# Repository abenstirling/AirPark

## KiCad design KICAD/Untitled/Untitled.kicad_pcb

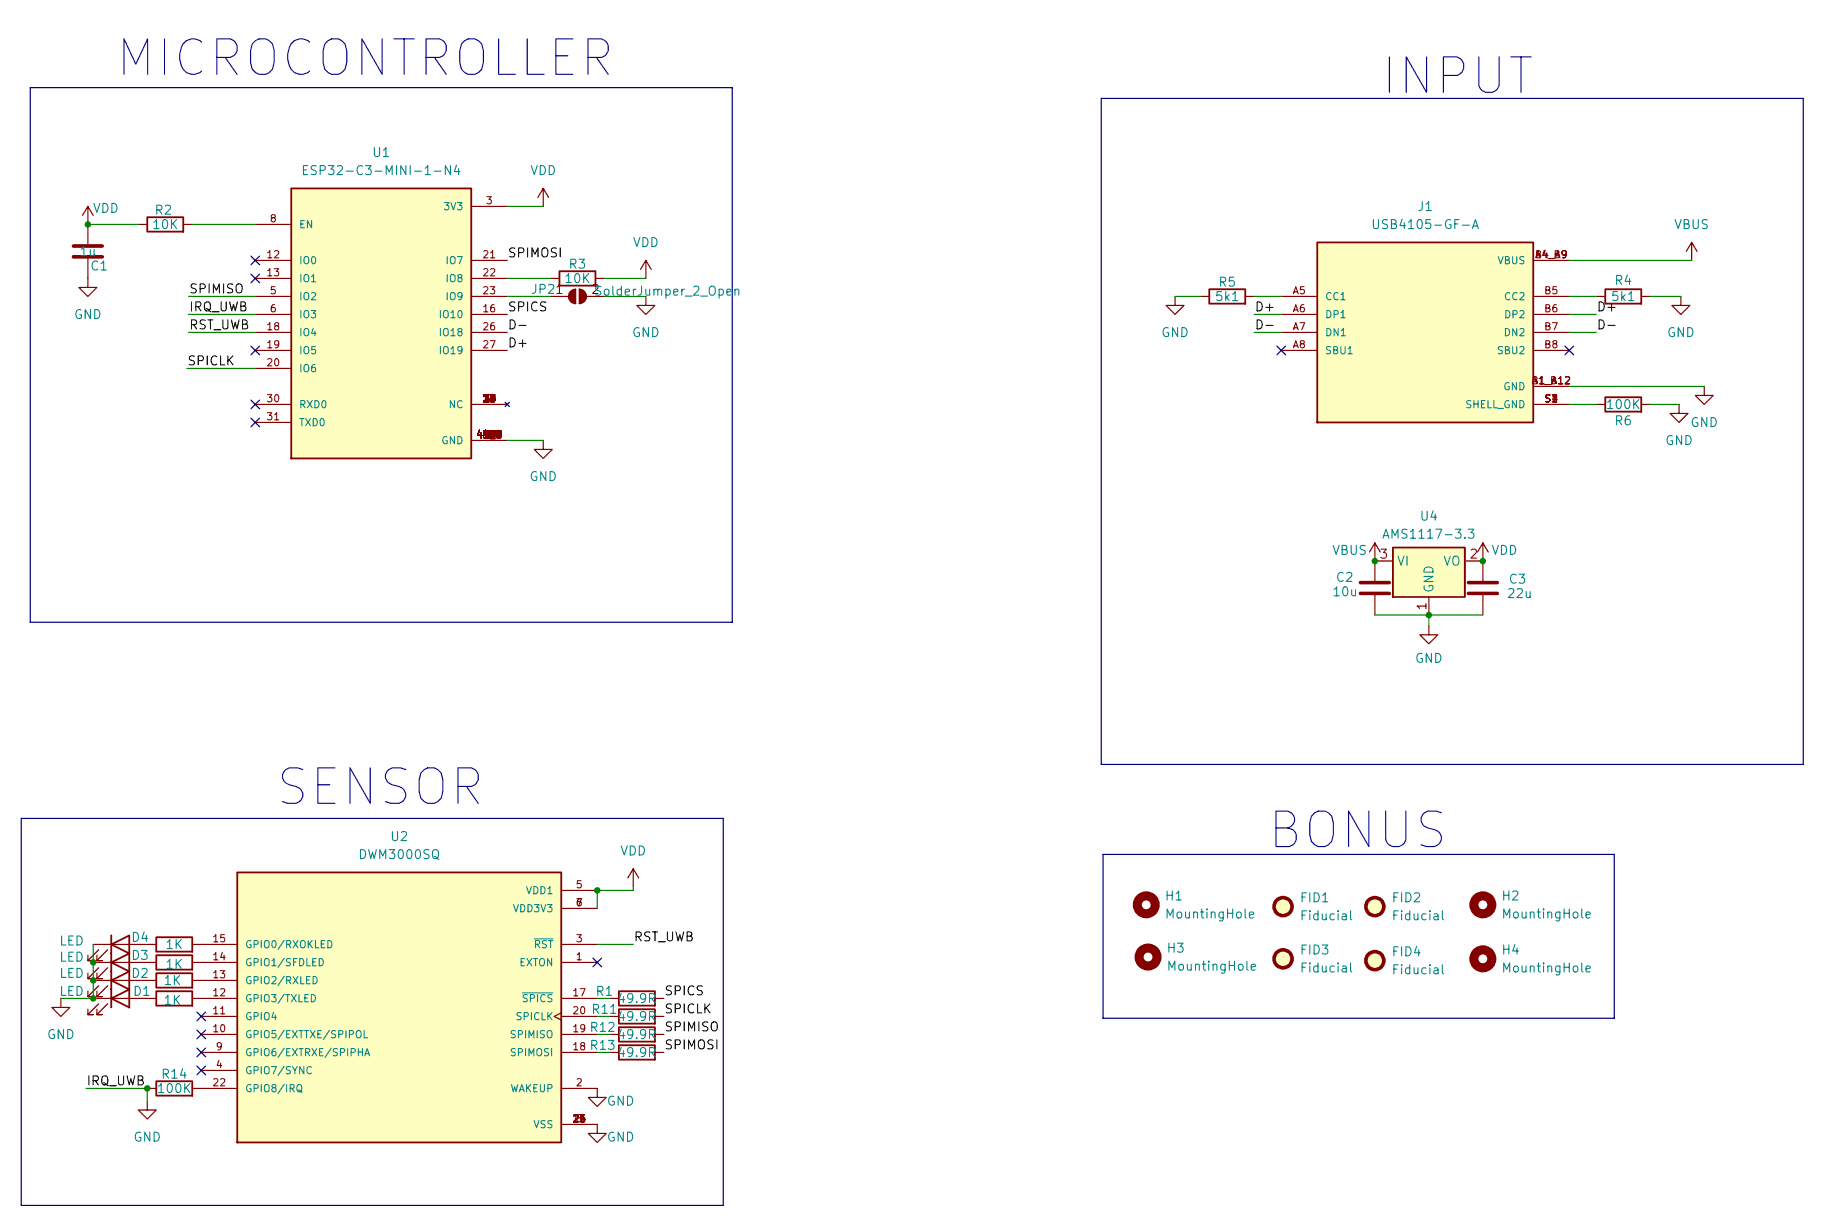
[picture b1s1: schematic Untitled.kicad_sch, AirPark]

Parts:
C1: 1u; C_0603_1608Metric
C2: 10u; C_0603_1608Metric
C3: 22u; C_0603_1608Metric
D1, D2, D3, D4: LED; LED_0603_1608Metric
FID1, FID2, FID3, FID4: Fiducial; Fiducial_1mm_Mask2mm
H1, H2, H3, H4: MountingHole; MountingHole_3.2mm_M3_DIN965_Pad
J1: USB4105-GF-A; GCT_USB4105-GF-A; PARTREV A3
JP2: SolderJumper_2_Open; SolderJumper-2_P1.3mm_Open_Pad1.0x1.5mm
R1, R11, R12, R13: 49.9R; R_0603_1608Metric
R2, R3: 10K; R_0603_1608Metric
R4, R5: 5k1; R_0603_1608Metric
R6, R14: 100K; R_0603_1608Metric
R7, R8, R9, R10: 1K; R_0603_1608Metric
U1: ESP32-C3-MINI-1-N4; XCVR_ESP32-C3-MINI-1-N4; PARTREV v1.0
U2: DWM3000SQ; XCVR_DWM3000SQ; PARTREV B
U4: AMS1117-3.3; SOT-223-3_TabPin2

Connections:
/D+: J1.A6 (DP1), J1.B6 (DP2), U1.27 (IO19)
/D-: J1.A7 (DN1), J1.B7 (DN2), U1.26 (IO18)
/RST_UWB: U1.18 (IO4), U2.3 (~RST)
/SPICLK: R11.2, U1.20 (IO6)
/SPICS: R1.2, U1.16 (IO10)
/SPIMISO: R12.2, U1.5 (IO2)
/SPIMOSI: R13.2, U1.21 (IO7)
GND: C1.2, C2.2, C3.2, D1.1 (K), D2.1 (K), D3.1 (K), D4.1 (K), J1.A1_B12 (GND), J1.B1_A12 (GND), JP2.2 (B), R4.2, R5.1, R6.2, R14.1, U1.1 (GND), U1.2 (GND), U1.6 (IO3), U1.11 (GND), U1.14 (GND), U1.36 (GND), U1.37 (GND), U1.38 (GND), U1.39 (GND), U1.40 (GND), U1.41 (GND), U1.42 (GND), U1.43 (GND), U1.44 (GND), U1.45 (GND), U1.46 (GND), U1.47 (GND), U1.48 (GND), U1.49_1 (GND), U1.49_2 (GND), U1.49_3 (GND), U1.49_4 (GND), U1.49_5 (GND), U1.49_6 (GND), U1.49_7 (GND), U1.49_8 (GND), U1.49_9 (GND), U1.50 (GND), U1.51 (GND), U1.52 (GND), U1.53 (GND), U2.2 (WAKEUP), U2.8 (VSS), U2.16 (VSS), U2.21 (VSS), U2.23 (VSS), U2.24 (VSS), U4.1 (GND)
unnamed: D1.2 (A), R10.1
unnamed: D2.2 (A), R7.1
unnamed: D3.2 (A), R8.1
unnamed: D4.2 (A), R9.1
unnamed: J1.A5 (CC1), R5.2
unnamed: J1.B5 (CC2), R4.1
unnamed: J1.S1 (SHELL_GND), J1.S2 (SHELL_GND), J1.S3 (SHELL_GND), J1.S4 (SHELL_GND), R6.1
unnamed: JP2.1 (A), U1.23 (IO9)
unnamed: R2.2, U1.8 (EN)
unnamed: R3.1, U1.22 (IO8)
unnamed: R9.2, U2.15 (GPIO0/RXOKLED)
unnamed: R8.2, U2.14 (GPIO1/SFDLED)
unnamed: R7.2, U2.13 (GPIO2/RXLED)
unnamed: R10.2, U2.12 (GPIO3/TXLED)
unnamed: R14.2, U2.22 (GPIO8/IRQ)
unnamed: R11.1, U2.20 (SPICLK)
unnamed: R12.1, U2.19 (SPIMISO)
unnamed: R13.1, U2.18 (SPIMOSI)
unnamed: R1.1, U2.17 (~SPICS)
VBUS: C2.1, J1.A4_B9 (VBUS), J1.B4_A9 (VBUS), U4.3 (VI)
VDD: C1.1, C3.1, R2.1, R3.2, U1.3 (3V3), U2.5 (VDD1), U2.6 (VDD3V3), U2.7 (VDD3V3), U4.2 (VO)

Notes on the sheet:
BONUS
MICROCONTROLLER
INPUT
SENSOR

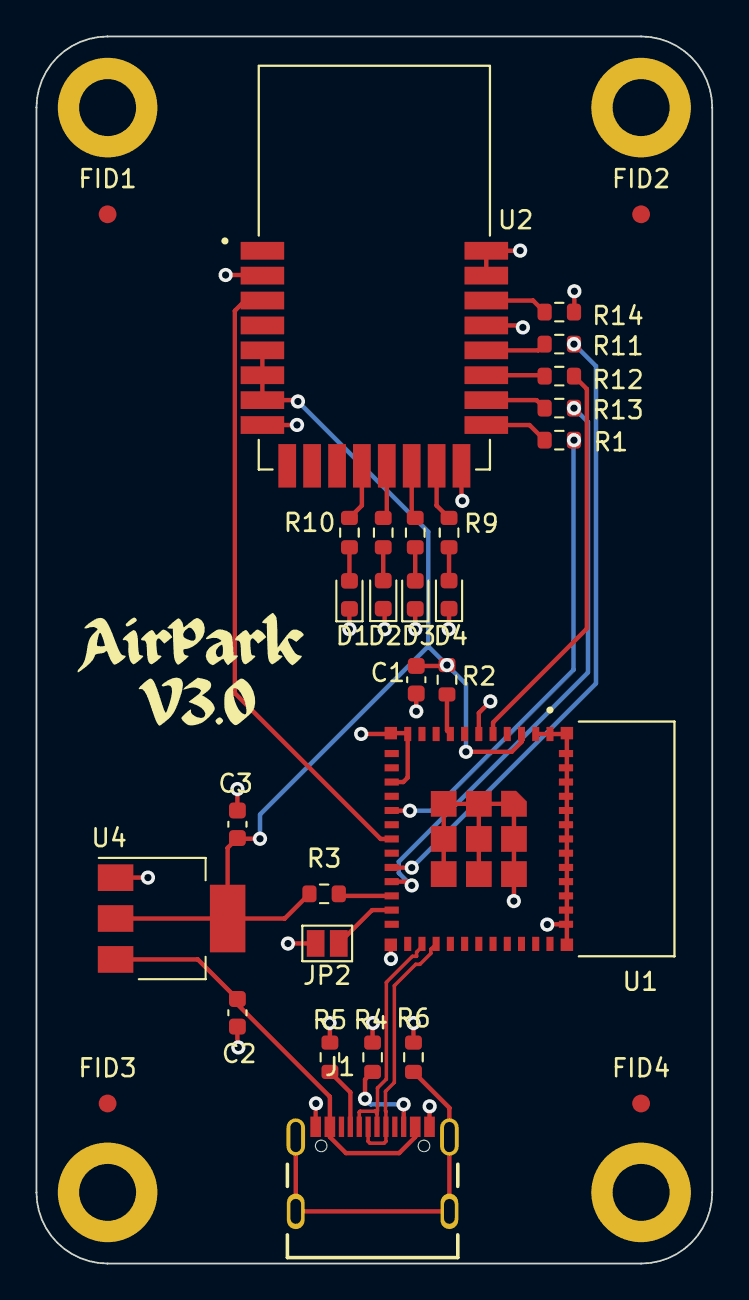
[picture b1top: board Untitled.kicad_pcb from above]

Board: 2 copper layers, 38.0 x 69.0 mm, 34 parts (0 on the bottom side), 29 nets.

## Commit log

2023-05-20 App and Kicad projects
2023-05-20 Removed untitled project
2023-05-20 Imports
2023-06-02 Datasheets
2023-08-22 adding components
